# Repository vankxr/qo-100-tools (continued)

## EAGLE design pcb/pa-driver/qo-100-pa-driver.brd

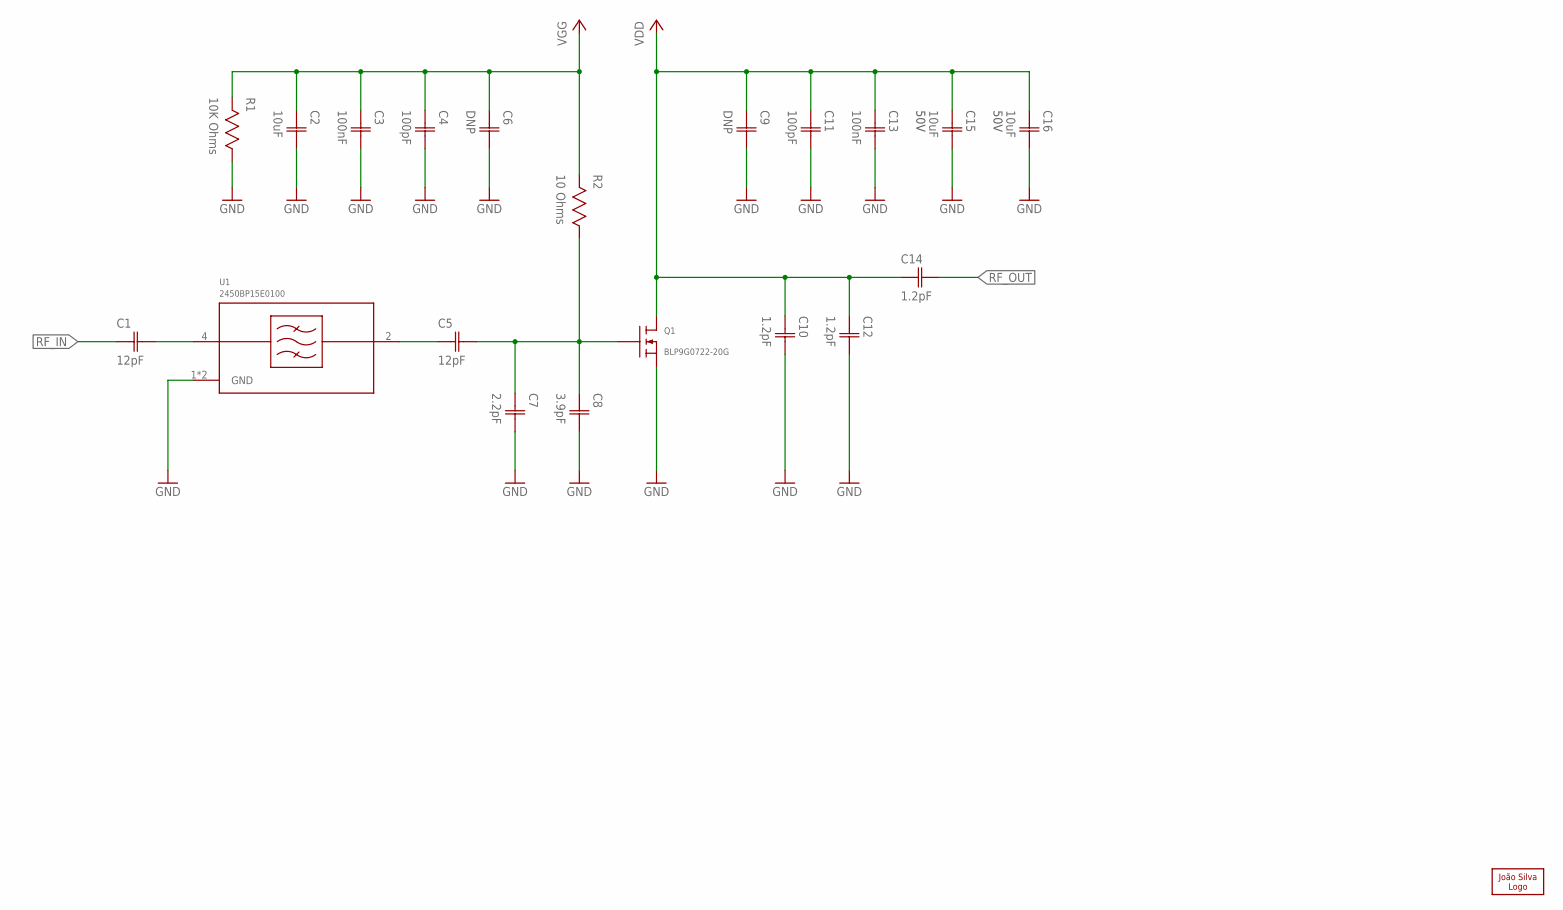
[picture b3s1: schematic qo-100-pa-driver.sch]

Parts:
C1, C5: 12pF; CAP0603
C2: 10uF; CAP0603
C3, C13: 100nF; CAP0603
C4, C11: 100pF; CAP0603
C6, C9: DNP; CAP0603
C7: 2.2pF; CAP0603
C8: 3.9pF; CAP0603
C10, C12, C14: 1.2pF; CAP0603
C15, C16: 10uF; CAP1206; VOLTAGE 50V
LOGO1: JS-5MM; JS_5MM
Q1: BLP9G0722-20G; SOT1483-1
R1: 10K Ohms; RES0603
R2: 10 Ohms; RES0603
U1: 2450BP15E0100

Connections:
GND: C2.2 (C2), C3.2 (C2), C4.2 (C2), C6.2 (C2), C7.2 (C2), C8.2 (C2), C9.2 (C2), C10.2 (C2), C11.2 (C2), C12.2 (C2), C13.2 (C2), C15.2 (C2), C16.2 (C2), Q1.3@0 (S), Q1.3@1 (S), Q1.3@2 (S), R1.1, U1.1 (GND), U1.3 (GND)
unnamed: C5.2 (C2), C7.1 (C1), C8.1 (C1), Q1.2 (G), R2.1
unnamed: C5.1 (C1), U1.2 (RFOUT)
unnamed: C1.2 (C2), U1.4 (RFIN)
RF_IN: C1.1 (C1)
RF_OUT: C14.2 (C2)
VDD: C9.1 (C1), C10.1 (C1), C11.1 (C1), C12.1 (C1), C13.1 (C1), C14.1 (C1), C15.1 (C1), C16.1 (C1), Q1.1 (D)
VGG: C2.1 (C1), C3.1 (C1), C4.1 (C1), C6.1 (C1), R1.2, R2.2

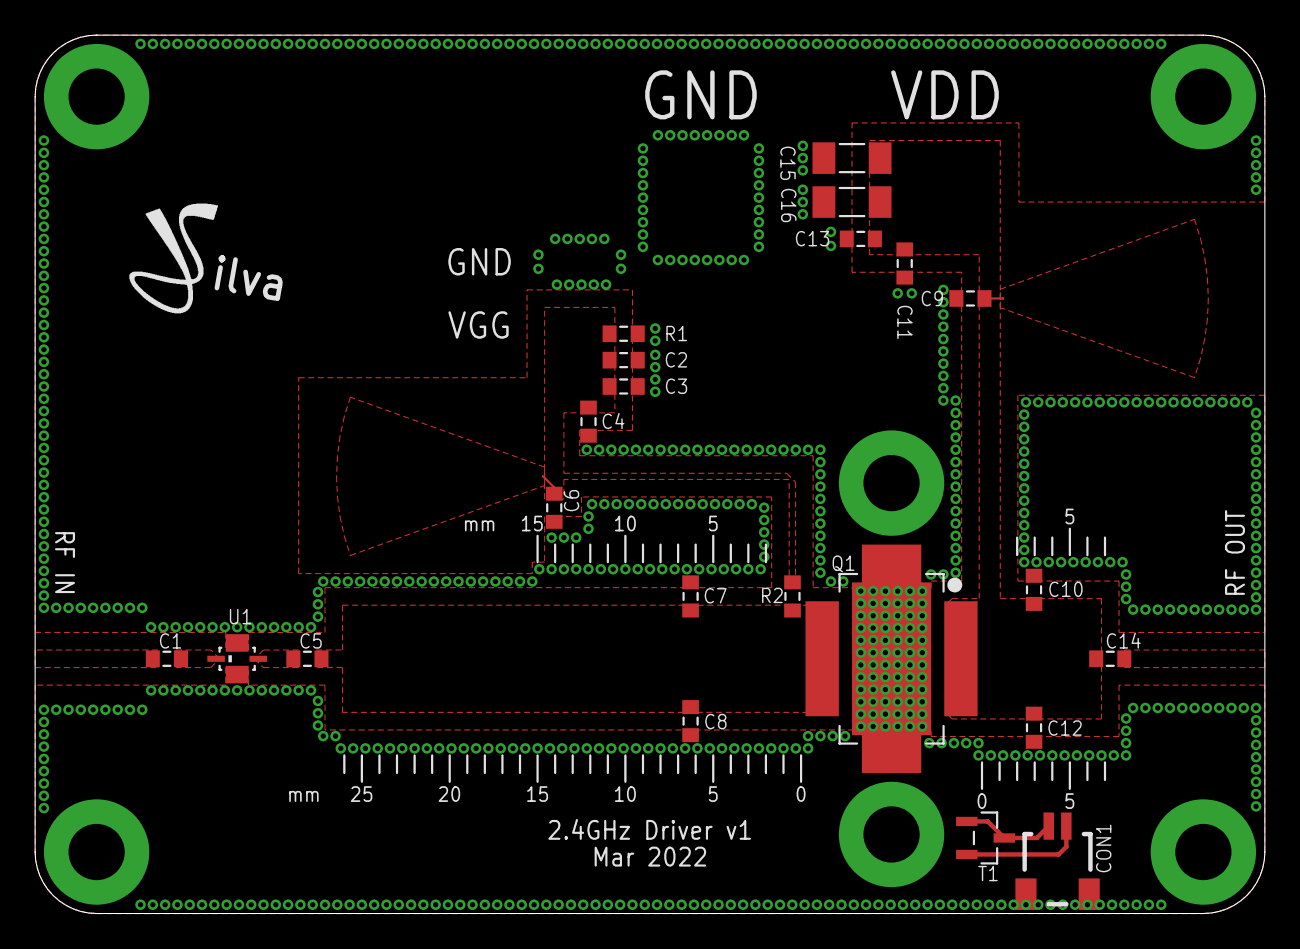
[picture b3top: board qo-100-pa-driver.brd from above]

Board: 2 copper layers, 70.0 x 50.0 mm, 23 parts (0 on the bottom side), 8 nets.

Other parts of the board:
CON1: 2P-SH-SIDE; SH-02-SIDE
T1: 2N3904; SOT23

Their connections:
unnamed: CON1.2, T1.2
unnamed: CON1.1, T1.1, T1.3

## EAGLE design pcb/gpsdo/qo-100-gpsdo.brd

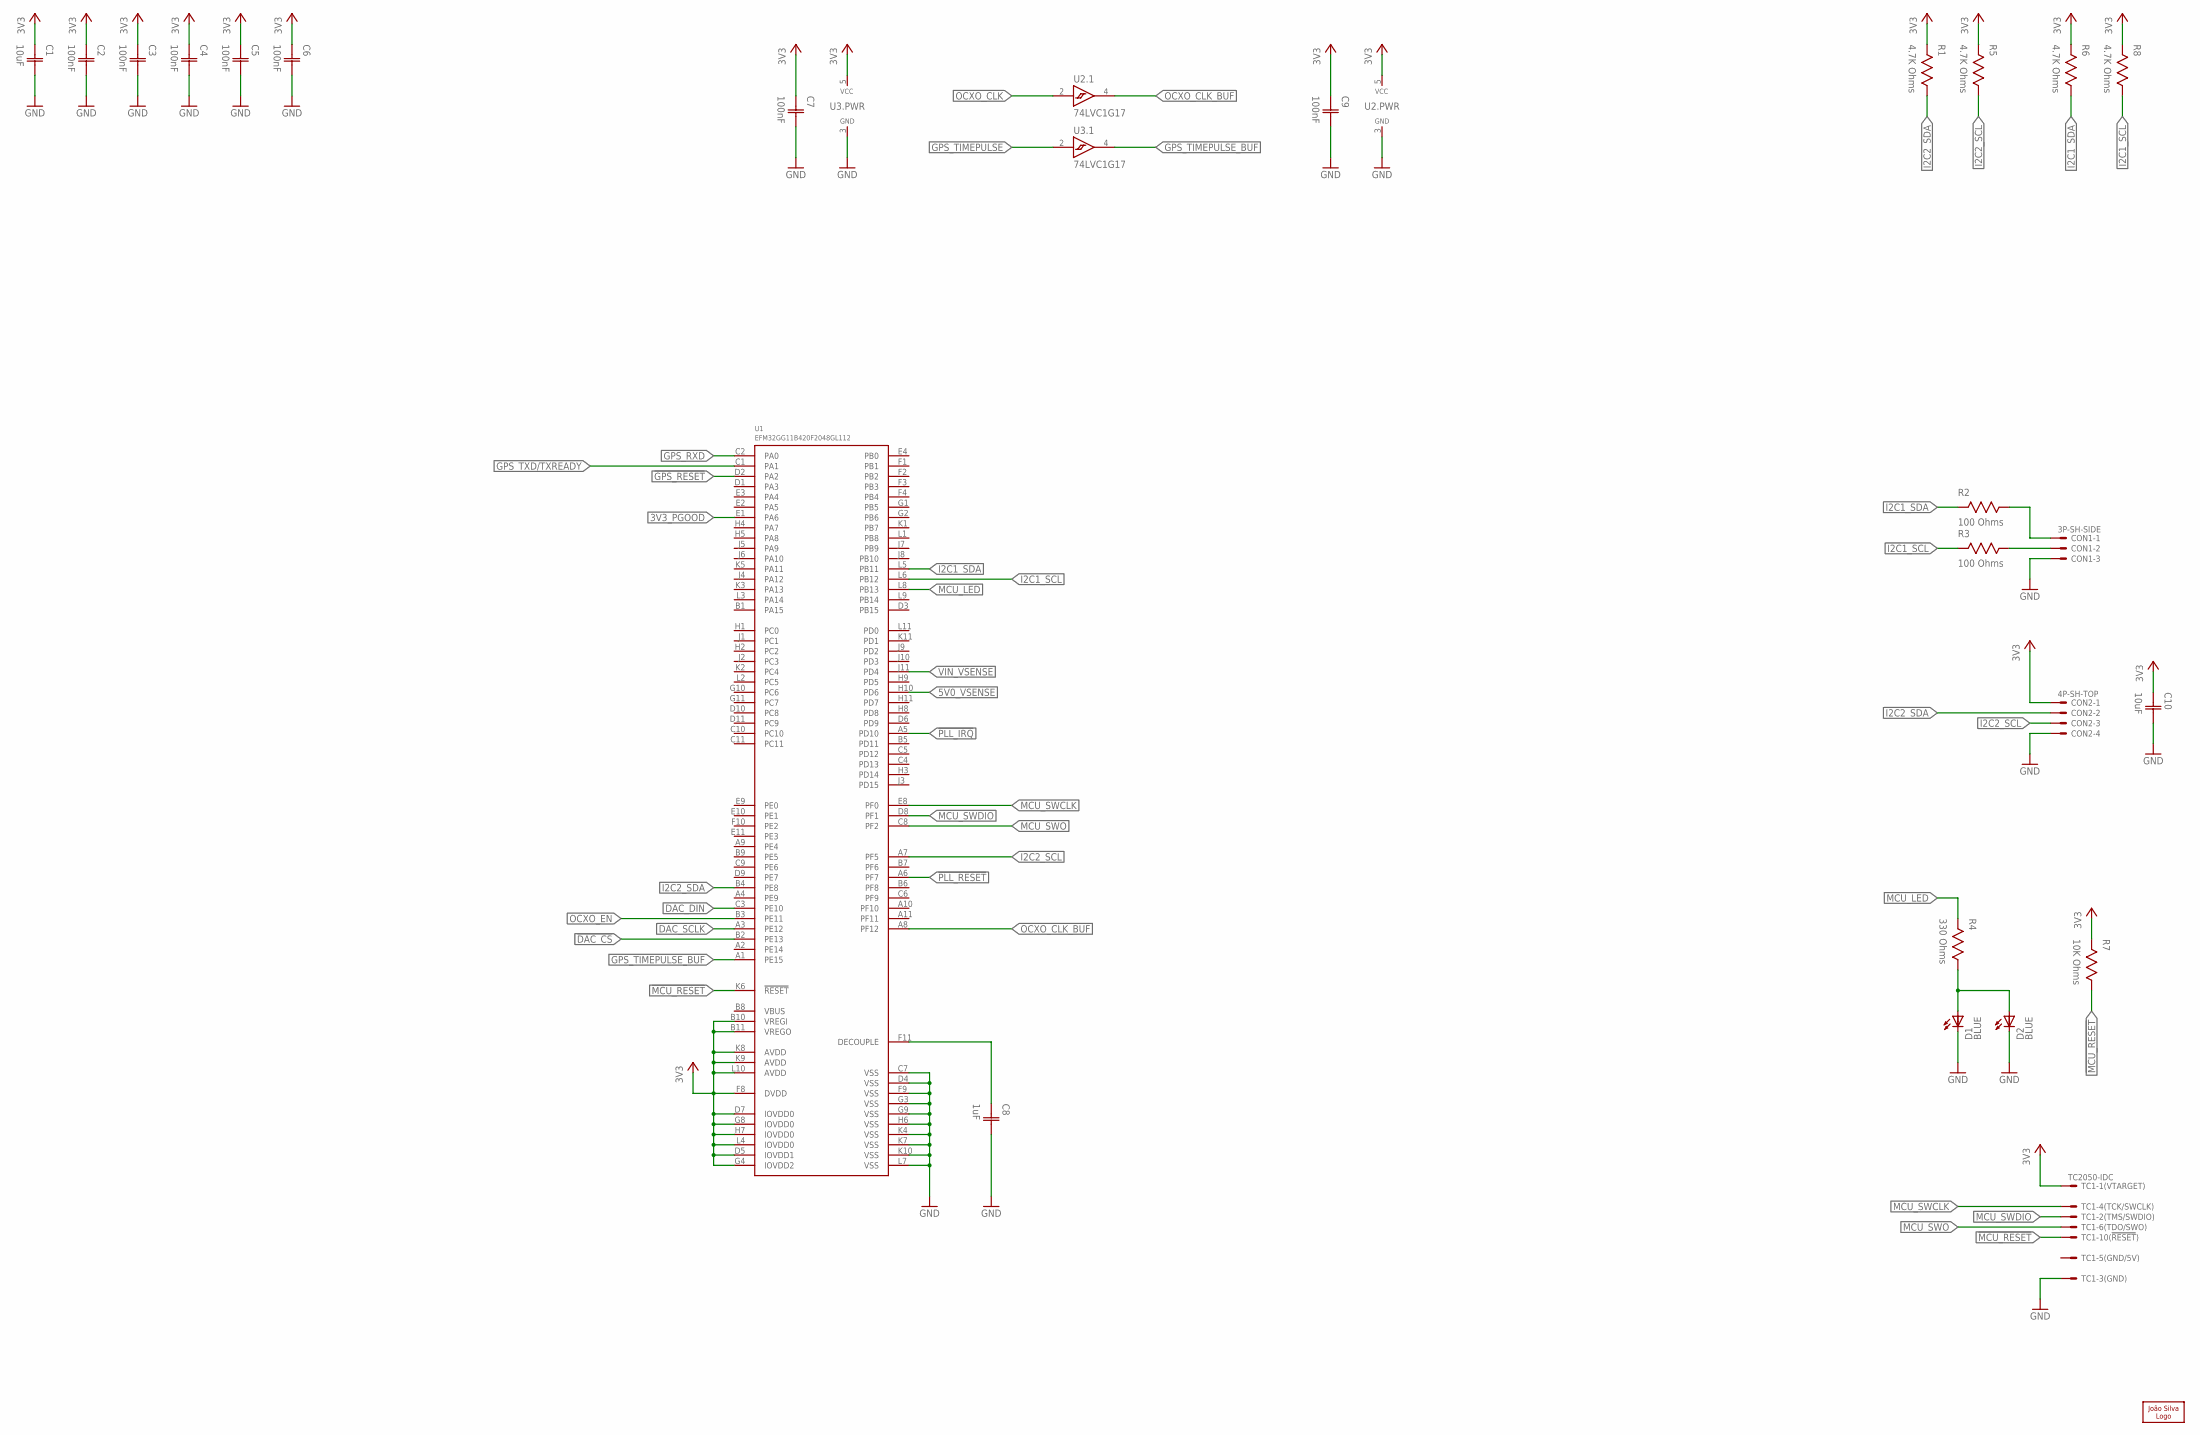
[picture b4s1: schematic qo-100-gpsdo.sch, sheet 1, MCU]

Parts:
C1, C10: 10uF; CAP0603
C2, C3, C4, C5, C6, C7, C9: 100nF; CAP0402
C8: 1uF; CAP0402
CON1: 3P-SH-SIDE; SH-03-SIDE
CON2: 4P-SH-TOP; SH-04-TOP
D1: LED0603; 0603
D2: LEDTH3MM; LED_3MM
LOGO1: JS-5MM; JS_5MM
R1, R5, R6, R8: 4.7K Ohms; RES0402
R2, R3: 100 Ohms; RES0402
R4: 330 Ohms; RES0402
R7: 10K Ohms; RES0402
TC1: TC2050-IDC
U1: EFM32GG11B420F2048GL112; BGA112
U2, U3: 74LVC1G17; SC70-5

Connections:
3V3: C1.1 (C1), C2.1 (C1), C3.1 (C1), C4.1 (C1), C5.1 (C1), C6.1 (C1), C7.1 (C1), C9.1 (C1), C10.1 (C1), CON2.1, R1.2, R5.2, R6.2, R7.2, R8.2, TC1.1, U1.B10 (VREGI), U1.B11 (VREGO), U1.D5 (IOVDD1), U1.D7 (IOVDD0), U1.F8 (DVDD), U1.G4 (IOVDD2), U1.G8 (IOVDD0), U1.H7 (IOVDD0), U1.K8 (AVDD), U1.K9 (AVDD), U1.L4 (IOVDD0), U1.L10 (AVDD), U2.5 (VCC), U3.5 (VCC); also elsewhere on the board
3V3_PGOOD: U1.E1 (PA6); also elsewhere on the board
5V0_VSENSE: U1.H10 (PD6); also elsewhere on the board
!DAC_CS: U1.B2 (PE13); also elsewhere on the board
!GPS_RESET: U1.D2 (PA2); also elsewhere on the board
!MCU_RESET: R7.1, TC1.10, U1.K6 (!RESET)
!PLL_IRQ: U1.A5 (PD10); also elsewhere on the board
!PLL_RESET: U1.A6 (PF7); also elsewhere on the board
DAC_DIN: U1.C3 (PE10); also elsewhere on the board
DAC_SCLK: U1.A3 (PE12); also elsewhere on the board
GND: C1.2 (C2), C2.2 (C2), C3.2 (C2), C4.2 (C2), C5.2 (C2), C6.2 (C2), C7.2 (C2), C8.2 (C2), C9.2 (C2), C10.2 (C2), CON1.3, CON2.4, D1.C, D2.K (C), TC1.3, U1.C7 (VSS), U1.D4 (VSS), U1.F9 (VSS), U1.G3 (VSS), U1.G9 (VSS), U1.H6 (VSS), U1.K4 (VSS), U1.K7 (VSS), U1.K10 (VSS), U1.L7 (VSS), U2.3 (GND), U3.3 (GND); also elsewhere on the board
GPS_RXD: U1.C2 (PA0); also elsewhere on the board
GPS_TIMEPULSE: U3.2 (A); also elsewhere on the board
GPS_TIMEPULSE_BUF: U1.A1 (PE15), U3.4 (Y)
GPS_TXD/TXREADY: U1.C1 (PA1); also elsewhere on the board
I2C1_SCL: R3.2, R8.1, U1.L6 (PB12)
I2C1_SDA: R2.2, R6.1, U1.L5 (PB11)
I2C2_SCL: CON2.3, R5.1, U1.A7 (PF5); also elsewhere on the board
I2C2_SDA: CON2.2, R1.1, U1.B4 (PE8); also elsewhere on the board
MCU_LED: R4.2, U1.L8 (PB13)
MCU_SWCLK: TC1.4, U1.E8 (PF0)
MCU_SWDIO: TC1.2, U1.D8 (PF1)
MCU_SWO: TC1.6, U1.C8 (PF2)
MCU_VCORE: C8.1 (C1), U1.F11 (DECOUPLE)
unnamed: CON1.2, R3.1
unnamed: CON1.1, R2.1
unnamed: D1.A, D2.A, R4.1
OCXO_CLK: U2.2 (A); also elsewhere on the board
OCXO_CLK_BUF: U1.A8 (PF12), U2.4 (Y)
OCXO_EN: U1.B3 (PE11); also elsewhere on the board
VIN_VSENSE: U1.J11 (PD4); also elsewhere on the board

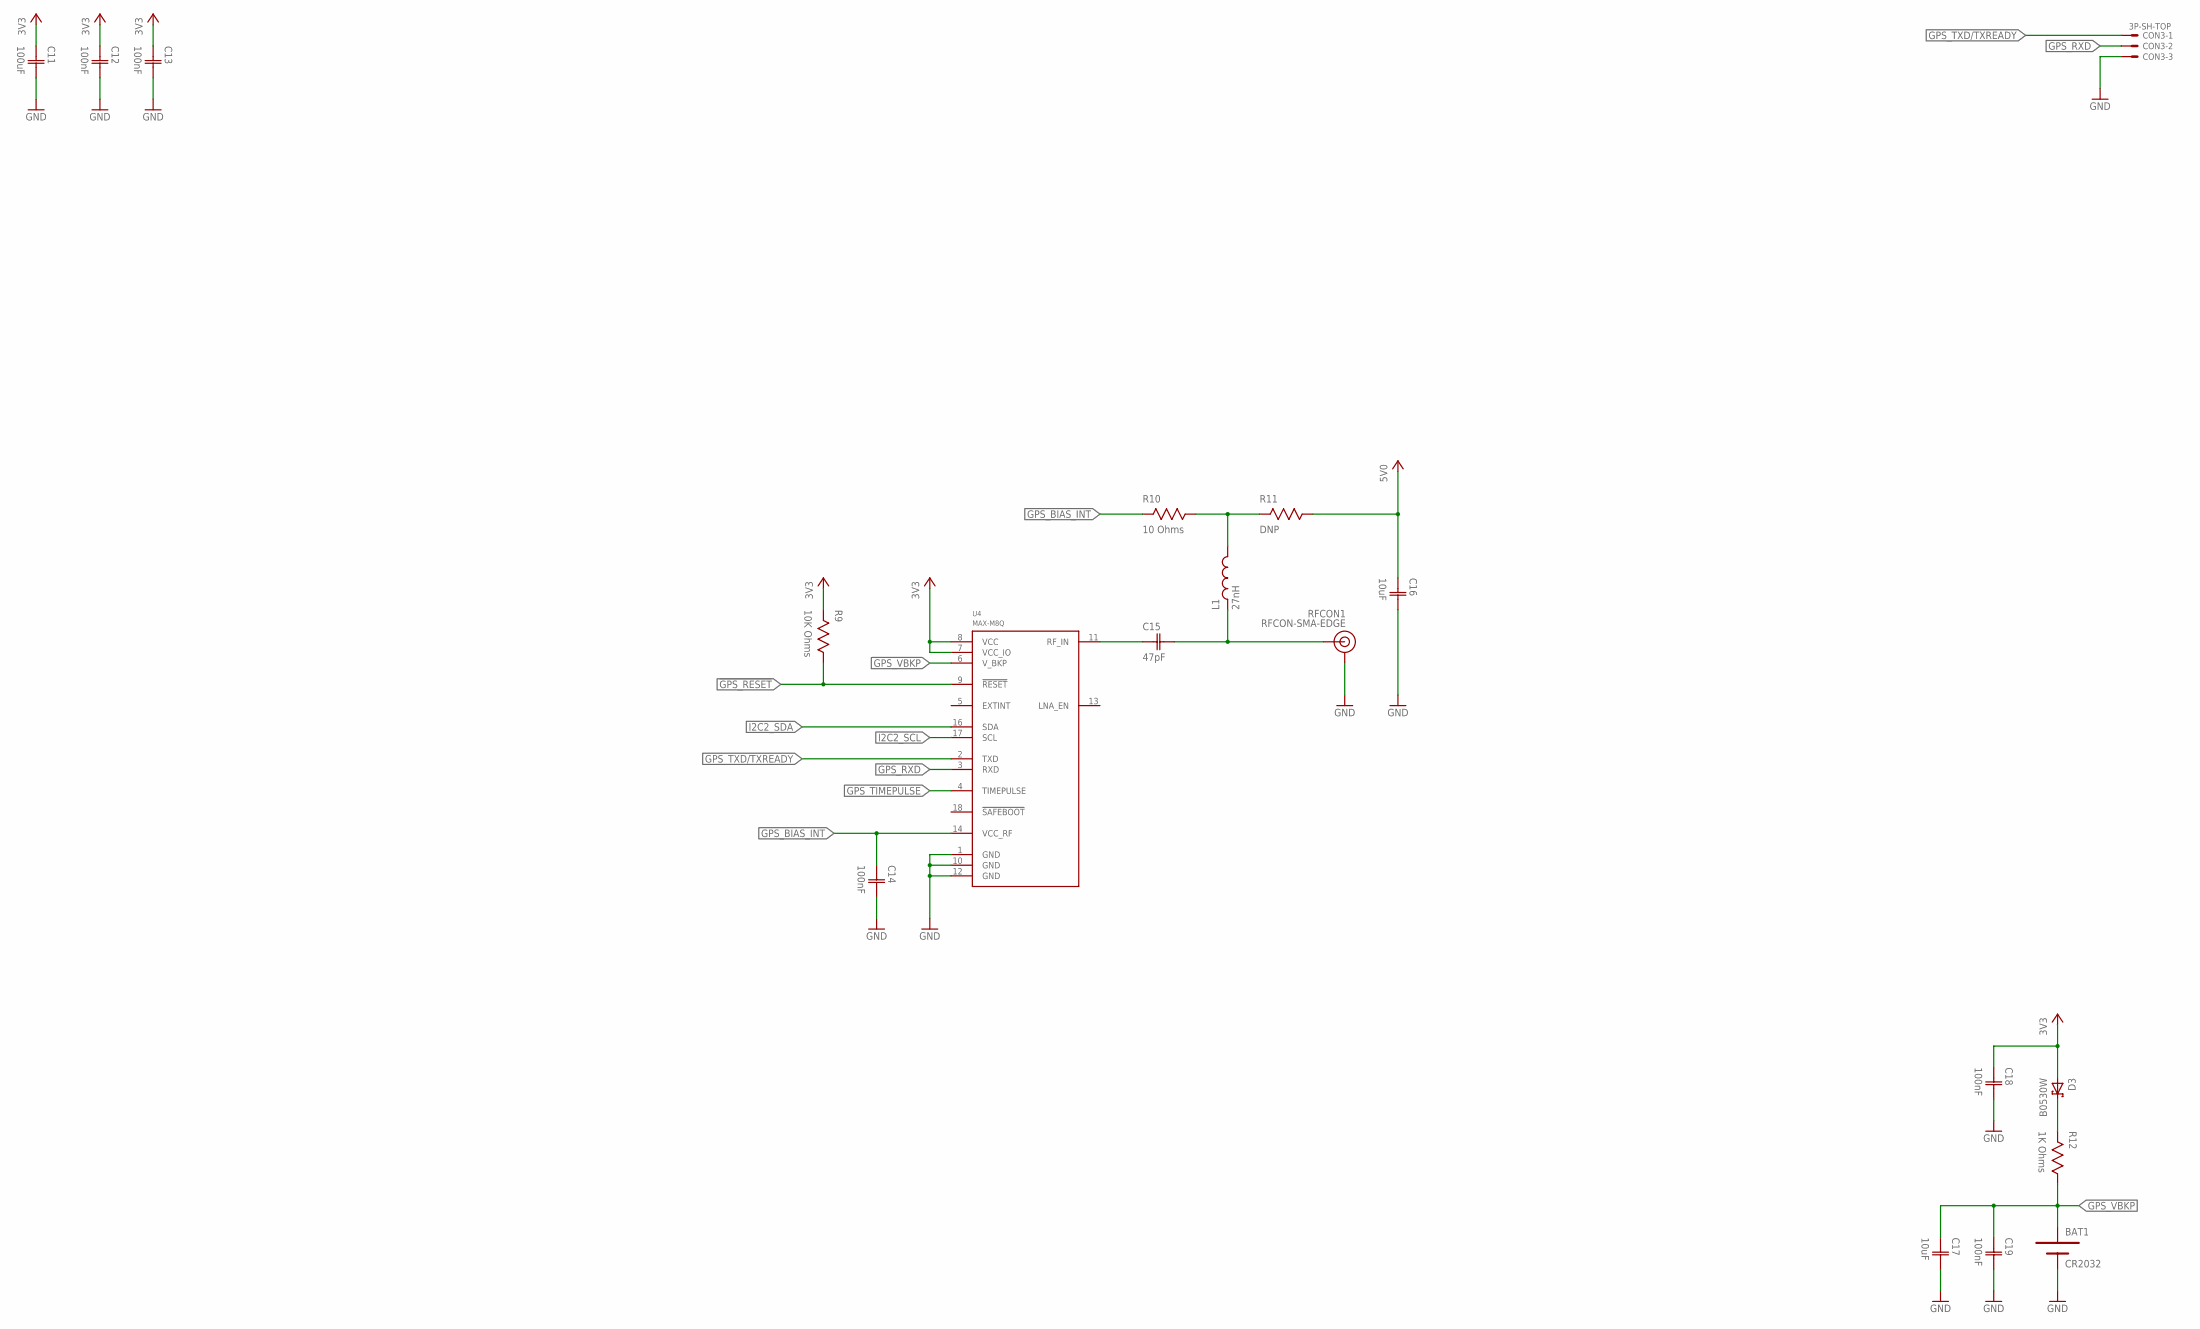
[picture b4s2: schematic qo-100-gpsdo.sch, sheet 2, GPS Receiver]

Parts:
BAT1: CR2032
C11: 100uF; CAP1206
C12, C13, C14, C18, C19: 100nF; CAP0402
C15: 47pF; CAP0402
C16, C17: 10uF; CAP0603
CON3: 3P-SH-TOP; SH-03-TOP
D3: B0530W; SOD-123
L1: 27nH; IND0805
R9: 10K Ohms; RES0402
R10: 10 Ohms; RES0603
R11: DNP; RES0603
R12: 1K Ohms; RES0402
RFCON1: RFCON-SMA-EDGE; SMA-EDGE
U4: MAX-M8Q; MAX-M8

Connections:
3V3: C11.1 (C1), C12.1 (C1), C13.1 (C1), C18.1 (C1), D3.A, R9.2, U4.7 (VCC_IO), U4.8 (VCC); also elsewhere on the board
5V0: C16.1 (C1), R11.1; also elsewhere on the board
!GPS_RESET: R9.1, U4.9 (!RESET); also elsewhere on the board
GND: BAT1.-, C11.2 (C2), C12.2 (C2), C13.2 (C2), C14.2 (C2), C16.2 (C2), C17.2 (C2), C18.2 (C2), C19.2 (C2), CON3.3, RFCON1.GND@0 (GND), RFCON1.GND@1 (GND), RFCON1.GND@2 (GND), RFCON1.GND@3 (GND), U4.1 (GND), U4.10 (GND), U4.12 (GND); also elsewhere on the board
GPS_BIAS_INT: C14.1 (C1), R10.2, U4.14 (VCC_RF)
GPS_RXD: CON3.2, U4.3 (RXD); also elsewhere on the board
GPS_TIMEPULSE: U4.4 (TIMEPULSE); also elsewhere on the board
GPS_TXD/TXREADY: CON3.1, U4.2 (TXD); also elsewhere on the board
GPS_VBKP: BAT1.+, C17.1 (C1), C19.1 (C1), R12.1, U4.6 (V_BKP)
I2C2_SCL: U4.17 (SCL); also elsewhere on the board
I2C2_SDA: U4.16 (SDA); also elsewhere on the board
unnamed: D3.C, R12.2
unnamed: C15.1 (C1), U4.11 (RF_IN)
unnamed: C15.2 (C2), L1.1, RFCON1.SIG (SIGNAL)
unnamed: L1.2, R10.1, R11.2

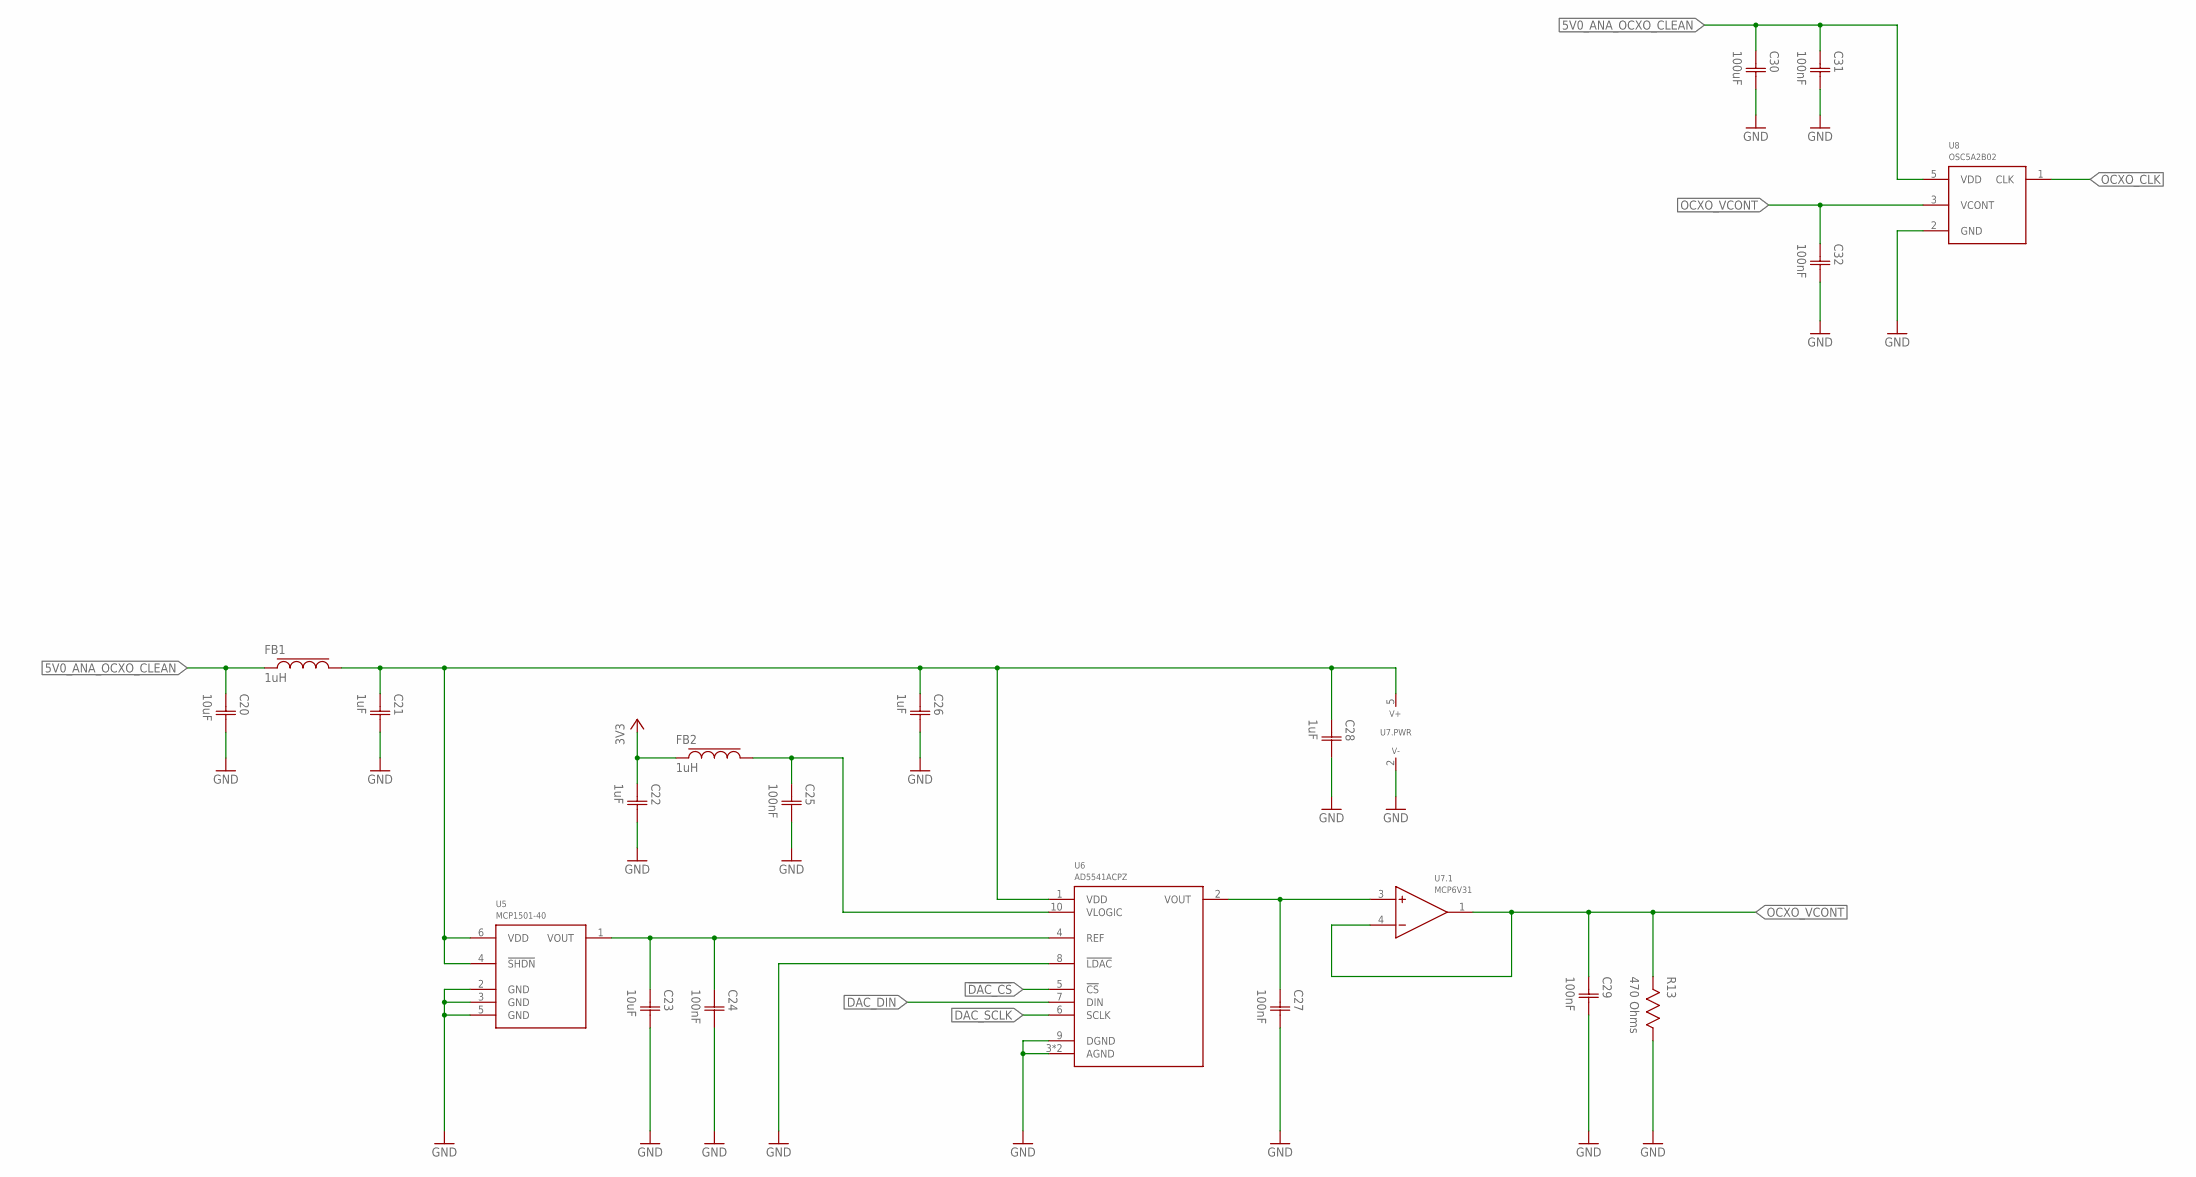
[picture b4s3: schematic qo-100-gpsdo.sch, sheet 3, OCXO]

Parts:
C20, C23: 10uF; CAP0603
C21, C22, C26, C28: 1uF; CAP0402
C24, C25, C27, C29, C31, C32: 100nF; CAP0402
C30: 100uF; CAP1206
FB1, FB2: 1uH; IND0603
R13: 470 Ohms; RES0402
U5: MCP1501-40; SOT23-6
U6: AD5541ACPZ; DFN10
U7: MCP6V31; SOT23-5
U8: OSC5A2B02

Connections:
3V3: C22.1 (C1), FB2.1; also elsewhere on the board
5V0_ANA_OCXO_CLEAN: C20.1 (C1), C30.1 (C1), C31.1 (C1), FB1.1, U8.5 (VDD); also elsewhere on the board
5V0_ANA_OCXO_CLEAN_FILT: C21.1 (C1), C26.1 (C1), C28.1 (C1), FB1.2, U5.4 (!SHDN), U5.6 (VDD), U6.1 (VDD), U7.5 (V+)
!DAC_CS: U6.5 (!CS); also elsewhere on the board
DAC_DIN: U6.7 (DIN); also elsewhere on the board
DAC_SCLK: U6.6 (SCLK); also elsewhere on the board
GND: C20.2 (C2), C21.2 (C2), C22.2 (C2), C23.2 (C2), C24.2 (C2), C25.2 (C2), C26.2 (C2), C27.2 (C2), C28.2 (C2), C29.2 (C2), C30.2 (C2), C31.2 (C2), C32.2 (C2), R13.1, U5.2 (GND), U5.3 (GND), U5.5 (GND), U6.3 (AGND), U6.8 (!LDAC), U6.9 (DGND), U6.11 (AGND), U7.2 (V-), U8.2 (GND); also elsewhere on the board
unnamed: C27.1 (C1), U6.2 (VOUT), U7.3 (+IN)
unnamed: C25.1 (C1), FB2.2, U6.10 (VLOGIC)
unnamed: C23.1 (C1), C24.1 (C1), U5.1 (VOUT), U6.4 (REF)
OCXO_CLK: U8.1 (CLK); also elsewhere on the board
OCXO_VCONT: C29.1 (C1), C32.1 (C1), R13.2, U7.1 (OUT), U7.4 (-IN), U8.3 (VCONT)

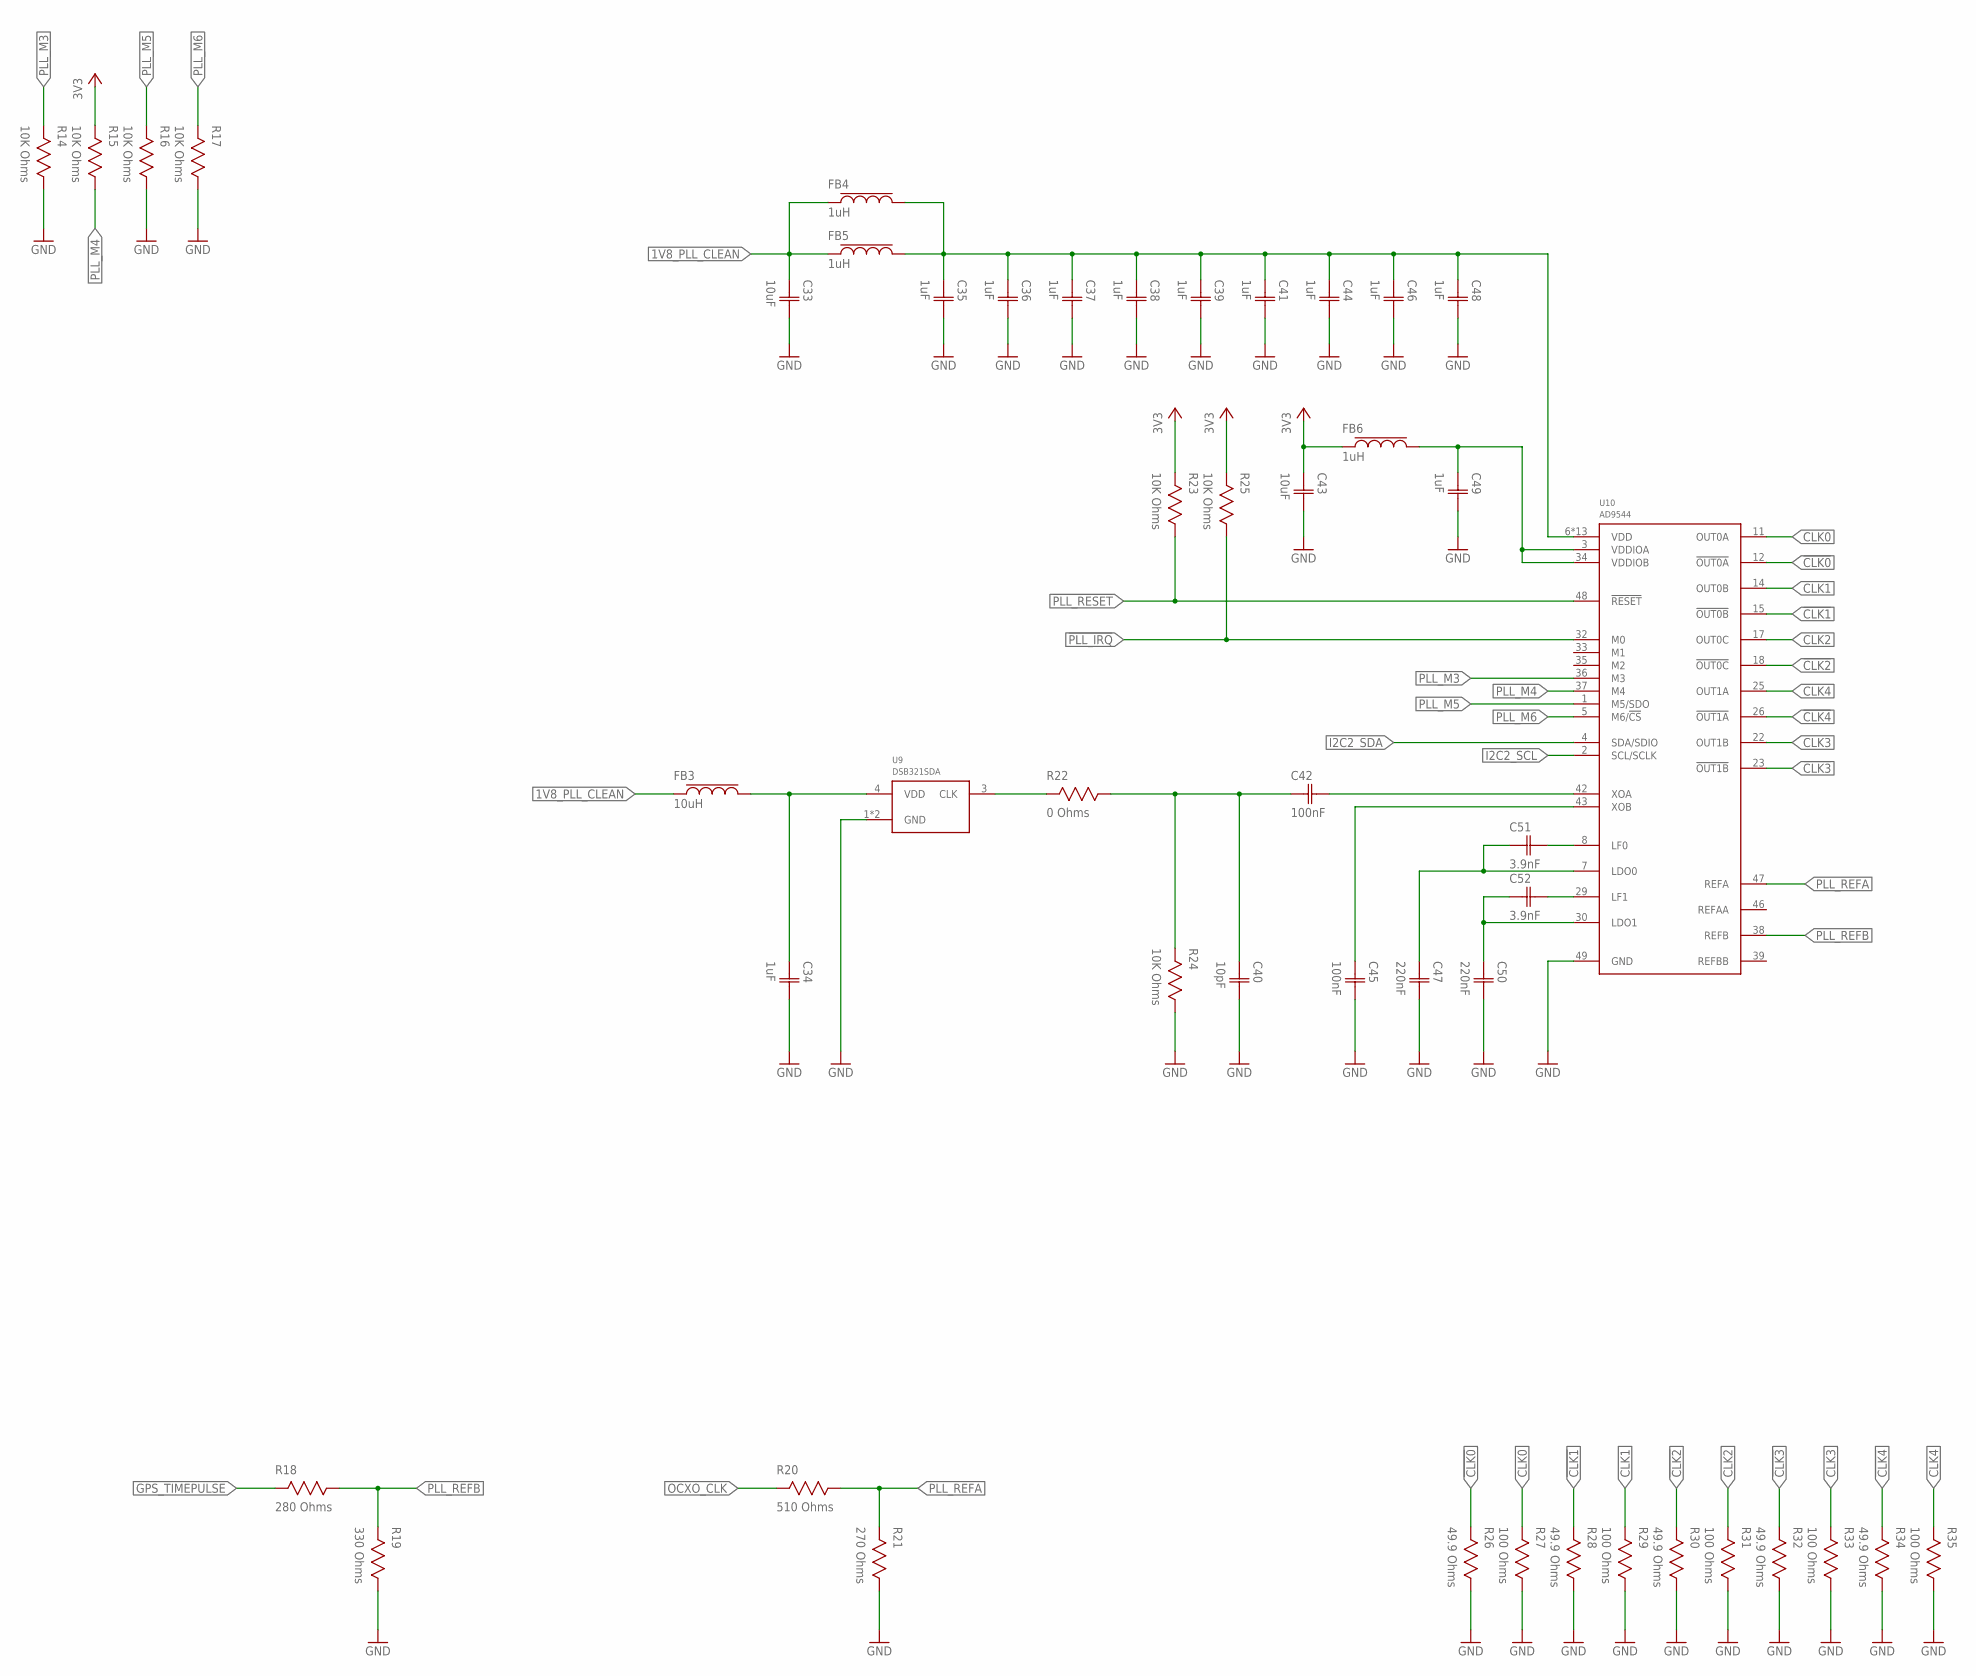
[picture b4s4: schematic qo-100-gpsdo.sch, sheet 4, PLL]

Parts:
C33, C43: 10uF; CAP0603
C34, C35, C36, C37, C38, C39, C41, C44, C46, C48, C49: 1uF; CAP0402
C40: 10pF; CAP0402
C42, C45: 100nF; CAP0402
C47, C50: 220nF; CAP0402
C51, C52: 3.9nF; CAP0402
FB3: 10uH; IND0603
FB4, FB5, FB6: 1uH; IND0603
R14, R15, R16, R17, R23, R24, R25: 10K Ohms; RES0402
R18: 280 Ohms; RES0402
R19: 330 Ohms; RES0402
R20: 510 Ohms; RES0402
R21: 270 Ohms; RES0402
R22: 0 Ohms; RES0402
R26, R28, R30, R32, R34: 49.9 Ohms; RES0402
R27, R29, R31, R33, R35: 100 Ohms; RES0402
U9: DSB321SDA; TCXO-3225
U10: AD9544; QFN48_2

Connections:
1V8_PLL_CLEAN: C33.1 (C1), FB3.1, FB4.1, FB5.1; also elsewhere on the board
1V8_PLL_CLEAN_FILT: C35.1 (C1), C36.1 (C1), C37.1 (C1), C38.1 (C1), C39.1 (C1), C41.1 (C1), C44.1 (C1), C46.1 (C1), C48.1 (C1), FB4.2, FB5.2, U10.6 (VDD), U10.9 (VDD), U10.10 (VDD), U10.13 (VDD), U10.19 (VDD), U10.20 (VDD), U10.24 (VDD), U10.27 (VDD), U10.28 (VDD), U10.31 (VDD), U10.40 (VDD), U10.41 (VDD), U10.45 (VDD)
3V3: C43.1 (C1), FB6.1, R15.2, R23.2, R25.2; also elsewhere on the board
3V3_PLL_FILT: C49.1 (C1), FB6.2, U10.3 (VDDIOA), U10.34 (VDDIOB)
!CLK0: R26.2, U10.12 (!OUT0A); also elsewhere on the board
!CLK1: R28.2, U10.15 (!OUT0B); also elsewhere on the board
!CLK2: R30.2, U10.18 (!OUT0C); also elsewhere on the board
!CLK3: R32.2, U10.23 (!OUT1B); also elsewhere on the board
!CLK4: R34.2, U10.26 (!OUT1A); also elsewhere on the board
!PLL_IRQ: R25.1, U10.32 (M0); also elsewhere on the board
!PLL_RESET: R23.1, U10.48 (!RESET); also elsewhere on the board
CLK0: R27.2, U10.11 (OUT0A); also elsewhere on the board
CLK1: R29.2, U10.14 (OUT0B); also elsewhere on the board
CLK2: R31.2, U10.17 (OUT0C); also elsewhere on the board
CLK3: R33.2, U10.22 (OUT1B); also elsewhere on the board
CLK4: R35.2, U10.25 (OUT1A); also elsewhere on the board
GND: C33.2 (C2), C34.2 (C2), C35.2 (C2), C36.2 (C2), C37.2 (C2), C38.2 (C2), C39.2 (C2), C40.2 (C2), C41.2 (C2), C43.2 (C2), C44.2 (C2), C45.2 (C2), C46.2 (C2), C47.2 (C2), C48.2 (C2), C49.2 (C2), C50.2 (C2), R14.1, R16.1, R17.1, R19.1, R21.1, R24.1, R26.1, R27.1, R28.1, R29.1, R30.1, R31.1, R32.1, R33.1, R34.1, R35.1, U9.1 (GND), U9.2 (GND), U10.49 (GND); also elsewhere on the board
GPS_TIMEPULSE: R18.2; also elsewhere on the board
I2C2_SCL: U10.2 (SCL/SCLK); also elsewhere on the board
I2C2_SDA: U10.4 (SDA/SDIO); also elsewhere on the board
unnamed: C40.1 (C1), C42.1 (C1), R22.1, R24.2
unnamed: R22.2, U9.3 (CLK)
unnamed: C50.1 (C1), C52.1 (C1), U10.30 (LDO1)
unnamed: C47.1 (C1), C51.1 (C1), U10.7 (LDO0)
unnamed: C52.2 (C2), U10.29 (LF1)
unnamed: C51.2 (C2), U10.8 (LF0)
unnamed: C45.1 (C1), U10.43 (XOB)
unnamed: C42.2 (C2), U10.42 (XOA)
unnamed: C34.1 (C1), FB3.2, U9.4 (VDD)
OCXO_CLK: R20.2; also elsewhere on the board
PLL_M3: R14.2, U10.36 (M3)
PLL_M4: R15.1, U10.37 (M4)
PLL_M5: R16.2, U10.1 (M5/SDO)
PLL_M6: R17.2, U10.5 (M6/!CS)
PLL_REFA: R20.1, R21.2, U10.47 (REFA)
PLL_REFB: R18.1, R19.2, U10.38 (REFB)
